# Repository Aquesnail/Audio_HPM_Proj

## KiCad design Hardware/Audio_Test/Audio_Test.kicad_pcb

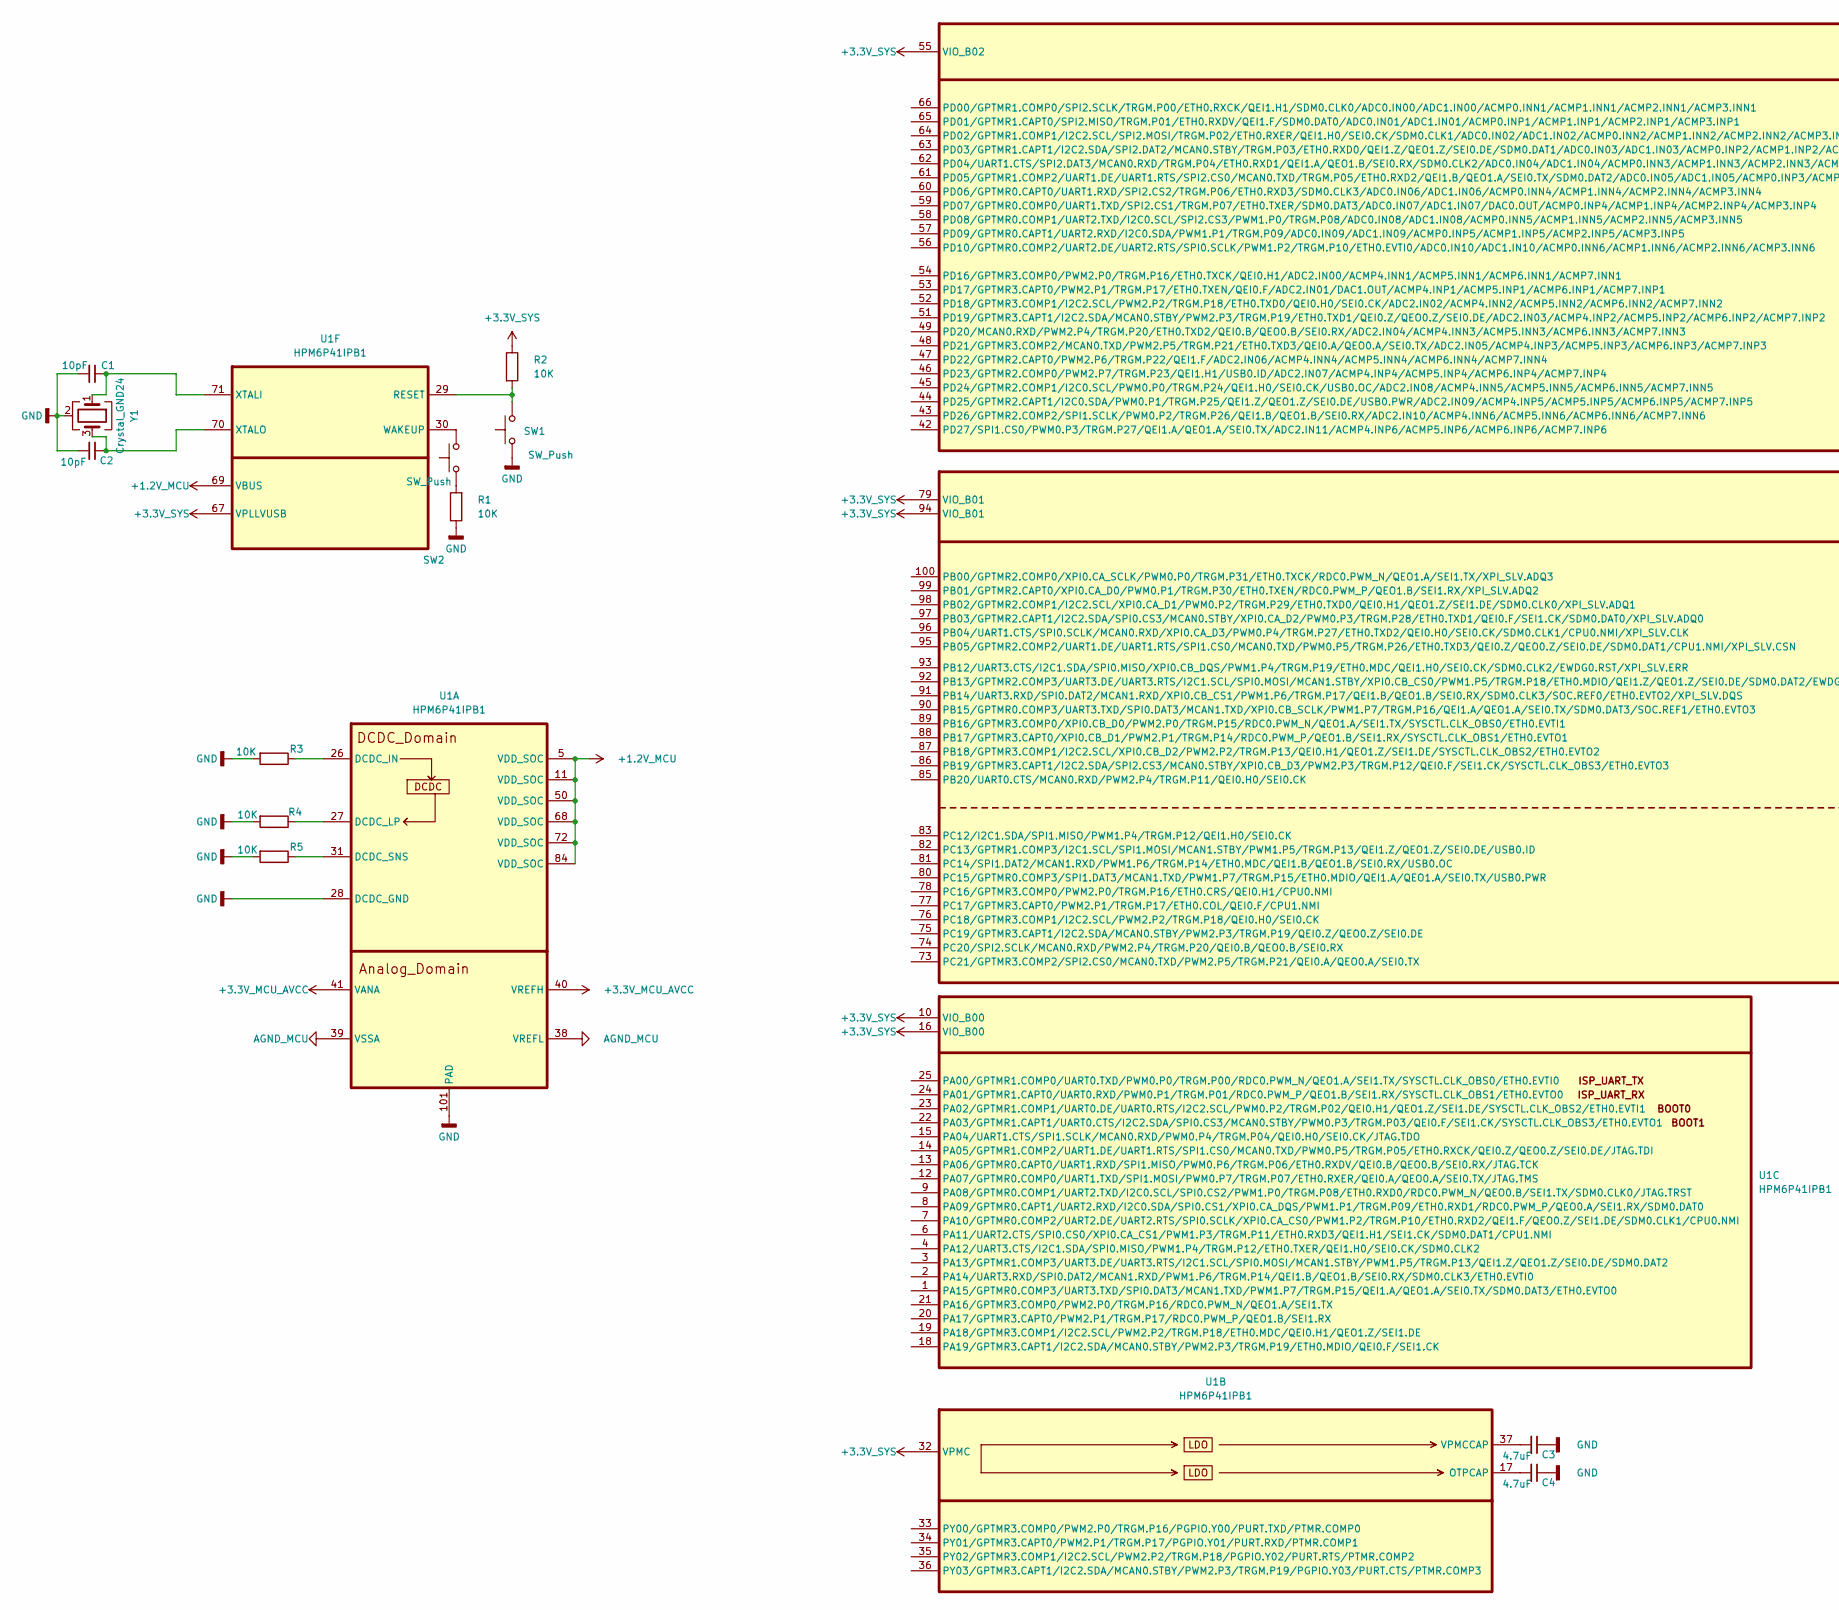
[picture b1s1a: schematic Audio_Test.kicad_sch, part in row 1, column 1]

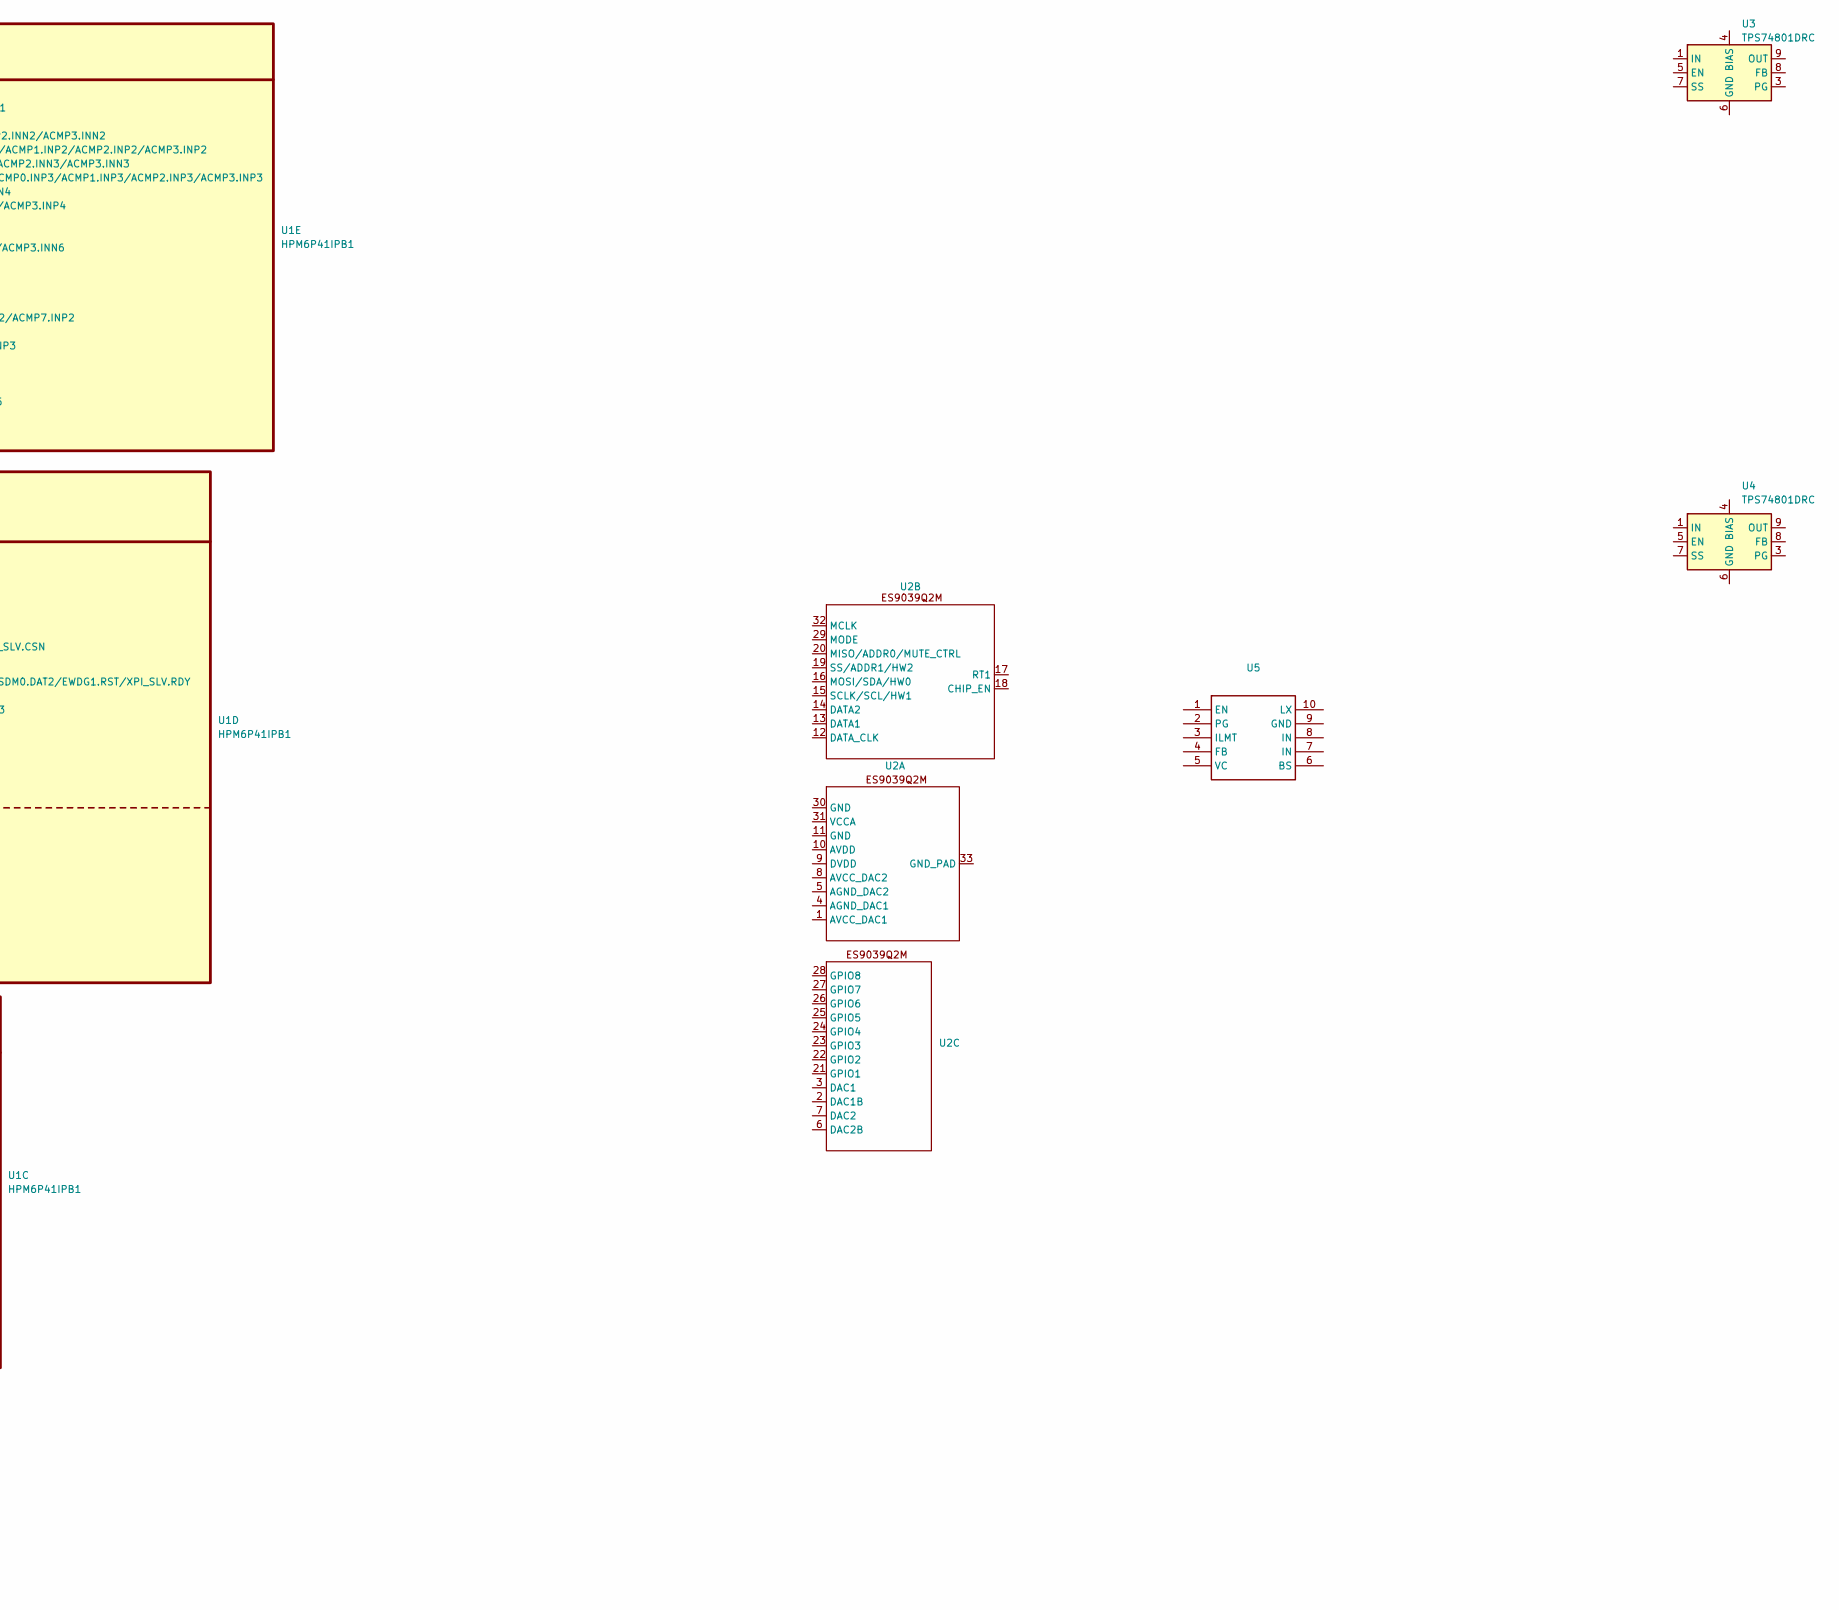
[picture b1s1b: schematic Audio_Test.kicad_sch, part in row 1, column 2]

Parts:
C1, C2: 10pF; C_0402_1005Metric
C3, C4: 4.7uF; C_0402_1005Metric
R1, R2, R3, R4, R5: 10K; R_0402_1005Metric
SW1, SW2: SW_Push; SW_Push_1P1T_NO_Vertical_Wuerth_434133025816
U1: HPM6P41IPB1; LQFP-100_14x14mm_P0.5mm_EP5.0x5.0mm
U2: QFN-32-1EP_5x5mm_P0.5mm_EP3.3x3.3mm
U3, U4: TPS74801DRC; VSON-10-1EP_3x3mm_P0.5mm_EP1.65x2.4mm_ThermalVias
U5: QFN-10_L3.0-W3.0-P0.45-TL_SILERGY; Manufacturer Part SY8368QNC; LCSC Part Name 高效同步降压DC-DC调节器
Y1: Crystal_GND24; Crystal_SMD_3225-4Pin_3.2x2.5mm

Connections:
+1.2V_MCU: U1.5 (VDD_SOC), U1.11 (VDD_SOC), U1.50 (VDD_SOC), U1.68 (VDD_SOC), U1.69 (VBUS), U1.72 (VDD_SOC), U1.84 (VDD_SOC)
+3.3V_MCU_AVCC: U1.40 (VREFH), U1.41 (VANA)
+3.3V_SYS: R2.1, U1.10 (VIO_B00), U1.16 (VIO_B00), U1.32 (VPMC), U1.55 (VIO_B02), U1.67 (VPLLVUSB), U1.79 (VIO_B01), U1.94 (VIO_B01)
AGND_MCU: U1.38 (VREFL), U1.39 (VSSA)
GND: C1.2, C2.2, C3.1, C4.1, R1.1, R3.2, R4.2, R5.2, SW1.1, U1.28 (DCDC_GND), U1.101 (PAD), Y1.2 (G), Y1.4 (G)
unnamed: R1.2, SW2.1
unnamed: R3.1, U1.26 (DCDC_IN)
unnamed: R4.1, U1.27 (DCDC_LP)
unnamed: R5.1, U1.31 (DCDC_SNS)
unnamed: C4.2, U1.17 (OTPCAP)
unnamed: C3.2, U1.37 (VPMCCAP)
unnamed: R2.2, SW1.2, U1.29 (RESET)
unnamed: SW2.2, U1.30 (WAKEUP)
unnamed: C1.1, U1.71 (XTALI), Y1.1
unnamed: C2.1, U1.70 (XTALO), Y1.3
unnamed: U3.6 (GND), U3.11 (GND)
unnamed: U3.1 (IN), U3.2 (IN)
unnamed: U3.9 (OUT), U3.10 (OUT)
unnamed: U4.6 (GND), U4.11 (GND)
unnamed: U4.1 (IN), U4.2 (IN)
unnamed: U4.9 (OUT), U4.10 (OUT)

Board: 4 copper layers, 17 parts (0 on the bottom side), 21 nets, no tracks yet.

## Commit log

2026-03-08 第二次提交，完成了系统的基本构建
2026-03-09 电源网络初步
2026-03-10 电源符号和封装，更换芯片为ES9039Q2M
